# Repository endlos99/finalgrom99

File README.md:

FinalGROM 99
============

The *TI 99/4A FinalGROM Cartridge*, or FinalGROM 99 for short, is a
cartridge for the TI 99/4A home computer that allows you to run ROM and GROM
cartridge images from an SD card.  It succeeds the [FlashROM 99][3] released
in 2016.

The FinalGROM 99 supports ROM images, GROM images, and mixed images of up to
1 MB in size that use the write-to-ROM bank switching scheme.  The cartridge
does not require the Peripheral Expansion Box and runs on both PAL and NTSC
consoles, including modified consoles with an F18A.  It will also run on
v2.2 consoles and enables those to run ROM-only programs.

The cartridge offers some advanced modes that provide RAM and GRAM to
programs.  It also allows a running program to reload another program from
SD card or to dump its state to SD card.  All firmware of the FinalGROM 99
can be updated by SD card.

The FinalGROM 99 is released as Open Source Hardware under the
[CERN OHL license][5] and the [GNU GPL license][6].  Both hardware design
files and firmware sources are available on [GitHub][2].

The project homepage with detailed instructions is located at [GitHub][1].

Using the FinalGROM 99
----------------------

Using the FinalGROM 99 is simple and doesn't require any special hardware or
software.

To begin, copy some cartridge dumps or other images files onto an SD or SDHC
card.  You can create directories to organize your programs.  Switch off the
TI 99 and plug in the FinalGROM 99, then insert the SD card into the
FinalGROM 99.  Switch on the TI 99 and wait until the activity indicator on
the FinalGROM 99 is no longer lit.

Press any key to bring up the TI menu screen.  You should see the `FINALGROM
99` entry.  Select it to start the image browser, where you can page through
the list of available image entries with `,`, `.`, `SPACE`, and number keys.
When you descend into a folder, the FinalGROM will reload its contents from
the SD card.  To go back up to the parent folder, select the special folder
`/ ..`.

Select the image you want to run.  The screen will show a loader animation
while the image loads.  Once the image has been loaded, it will start
automatically.  The SD card is now no longer required and may be removed.

If only one image is found on the SD card, it is loaded immediately without
the need to select it first.  This method ensures maximum compatibility.
Note that ROM images loaded as single-image SD card will not run on v2.2
consoles!

If you want to run a different program from the SD card, reset the TI 99 by
pressing `FCTN-=` and then reset the FinalGROM 99 by pushing the reset
button.  If you do not reset the FinalGROM 99, the TI menu will show only
the previously selected image.  Alternatively, you can power cycle the
console, which will reset both TI 99 and FinalGROM 99.

For detailed usage information please refer to the [FinalGROM 99 homepage][1].

Building the FinalGROM 99
-------------------------

The [GitHub repository][2] contains all hardware design files and software
sources required to build the FinalGROM 99.

Building the FinalGROM 99 is slightly more involved than building its
predecessor [FlashROM 99][3], as the FinalGROM 99 uses surface-mounted
devices (SMD), of which two are programmable.  For starters, this
[video tutorial][12] shows how to solder SMD ICs by hand.

### Hardware

To build the FinalGROM 99, you need the following components:

- 1x FinalGROM 99 PCB
- 1x Xilinx XC95144XL-10TQ100 (TQFP-100)
- 1x Atmel ATmega 328P (TQPF-32)
- 1x Cypress SRAM CY62158EV30LL-45ZSXI (TSOP-44)
- 1x On Semiconductor Voltage Converter NCP1117ST33T3G (SOT-223)
- 12x 100 nF ceramic capacitors (SMD 0603)
- 2x 10 uF tantalum capacitors (SMD 0603)
- 2x 330 Ohm resistor (SMD 0603)
- 2x 10 kOhm resistor (SMD 0603)
- 1x LED 3-5 mm (through-hole)
- 2x micro push button (through-hole)
- 1x 2x3 socket (through-hole)
- 1x SD socket or Arduino SD shield

The FinalGROM 99 board was designed with [KiCad][7], a cross platform and
open source electronics design automation suite.  The design files are
stored in `pcb/` in the [repository][2].

The size of the 330 Ohm resistor depends on the color and brightness of your
LED.  For bright, red LEDs, 330 Ohm is a suitable value.

Both LED and push buttons are through-hole components, so that they can be
mounted on a cartridge shell and connected by wires to the board.

For the SD socket, you need a socket that has two little nubs at the bottom
of the socket.  Your best source for these is eBay, but check the pictures
before you buy.  Alternatively, you may use an Arduino SD shield that is
readily available online.  Make sure to pick a module that matches the
pin-out of the reference module shown below.  Note that the 5V input is not
used, so potential substitutes must be powered by 3.3V.

With some work, the FinalGROM 99 can be mounted in a standard TI 99
cartridge shell.

Please note that I don't offer carts, boards, or parts myself.

### Software

The firmware for the ATmega 328P consists of two components.  The `avr/`
folder contains the microcontroller logic for accessing the SD card,
generating the image browser, loading the selected image, and controlling
the CPLD.  The included bootloader enables firmware updates from an SD card.

The `ti/` folder contains TI 99 assembly sources for the image browser, the
GPL wrapper, and the help viewer.  The assembled machine code is embedded in
the microcontroller and loaded into RAM during operation.

To build the software, first run the `make.py` script in the `ti` folder.
You will need both `xas99` and `xga99` assemblers from the [xdt Suite][4] to
assemble the sources.  The script will also convert the generated machine
code into C code for the microcintroller.

    $ cd ti/
    $ ./make.py

The next step is to compile the microcontroller and bootloader code in
`avr/`.  The included `Makefile`s make the compilation trivial:

    $ cd avr/
    $ make
    $ cd boot/
    $ make

The last build yields a `package.hex` file containing both machine code
and bootloader.  You can flash the file to the ATmega 328P using
[`avrdude`][8] or any other programmer:

    $ avrdude -p m328p -P /dev/ttyACM0 -c stk500 -U flash:w:package.hex

Additionally, you need to program the lower fuse bits of the 328P so that it
runs at 8 Mhz:

    $ avrdude -p m328p -P /dev/ttyACM0 -c stk500 -U lfuse:w:0xe2:m

If you're using a different tool chain make sure to set `CKSEL3..0` in the
lower fuse byte to `0100`.  (Note that `0` means "programmed"/checked, and
`1` means "unprogrammed"/unchecked).

You can verify that you're running at the right clock speed by resetting
the FinalGROM 99 with no SD card inserted: The LED should blink about once
per second.

For future updates, you may copy the file `UPDATE.AVR` generated by the
first make in `avr/` to an SD card and start the FinalGROM 99 with it.  This
procedure will update the microcontroller similar to `avrdude`, but it does
not touch the bootloader.

Programming the CPLD requires the Xilinx [ISE 14.7 Web Pack][9] to generate
a JEDEC file or an XSVF file.  ISE Web Pack is freely available for Windows
and Linux.  After the installation, open ISE and open the project in
`vhdl/`.  Click on the little green arrow next to the process window to
generate a JEDED file.

The microcontroller contains an XSVF player to program the CPLD without JTAG
cable.  Generate the necessary XSVF file from the JEDED file by running (you
may have to adjust the path in `impact-batch`)

    $ cd vhdl/src
	$ ./impact-batch fg99-xsvf

Copy the resulting `.XSVF` file as `UPDATE.PLD` to an SD card and start the
FinalGROM 99 with it.  The cart will program the CPLD just like a JTAG cable
would do.

Once microcontroller and CPLD have been programmed, the assembled FinalGROM
99 is ready to use.

About the Project
-----------------

The TI 99/4A FinalGROM Cartridge is Open Source Hardware released under the
[CERN OHL license][5], in the hope that TI 99 enthusiasts may find it
useful.  Software components are released under the [GNU GPL license][6].

The microcontroller code uses a modified version of the [Petit FatFs][10]
library and an adapted version of the Xilinx [Application Note 58][11] code.

Heartfelt thanks go to Erik Spiehl (speccery) for helping me analyze an
electrical problem on the development boards, and to Jim Brain (Brain) for
showing me how to replace the Arduino shields by plain SD sockets.

Contributions to both hardware and software are very welcome!  Please email
feedback, support questions, inquiries for parts, and bug reports to the
developer at <r@0x01.de>.

[1]: https://endlos99.github.io/finalgrom99
[2]: https://github.com/endlos99/finalgrom99
[3]: https://endlos99.github.io/flashrom99
[4]: https://endlos99.github.io/xdt99
[5]: http://www.ohwr.org/projects/cernohl/wiki
[6]: http://www.gnu.org/licenses/gpl.html
[7]: http://kicad.org
[8]: http://www.nongnu.org/avrdude/
[9]: https://www.xilinx.com/products/design-tools/ise-design-suite/ise-webpack.html
[10]: http://elm-chan.org/fsw/ff/00index_p.html
[11]: http://www.xilinx.com/support/documentation/application_notes/xapp058.pdf
[12]: https://www.youtube.com/watch?v=6PB0u8irn-4

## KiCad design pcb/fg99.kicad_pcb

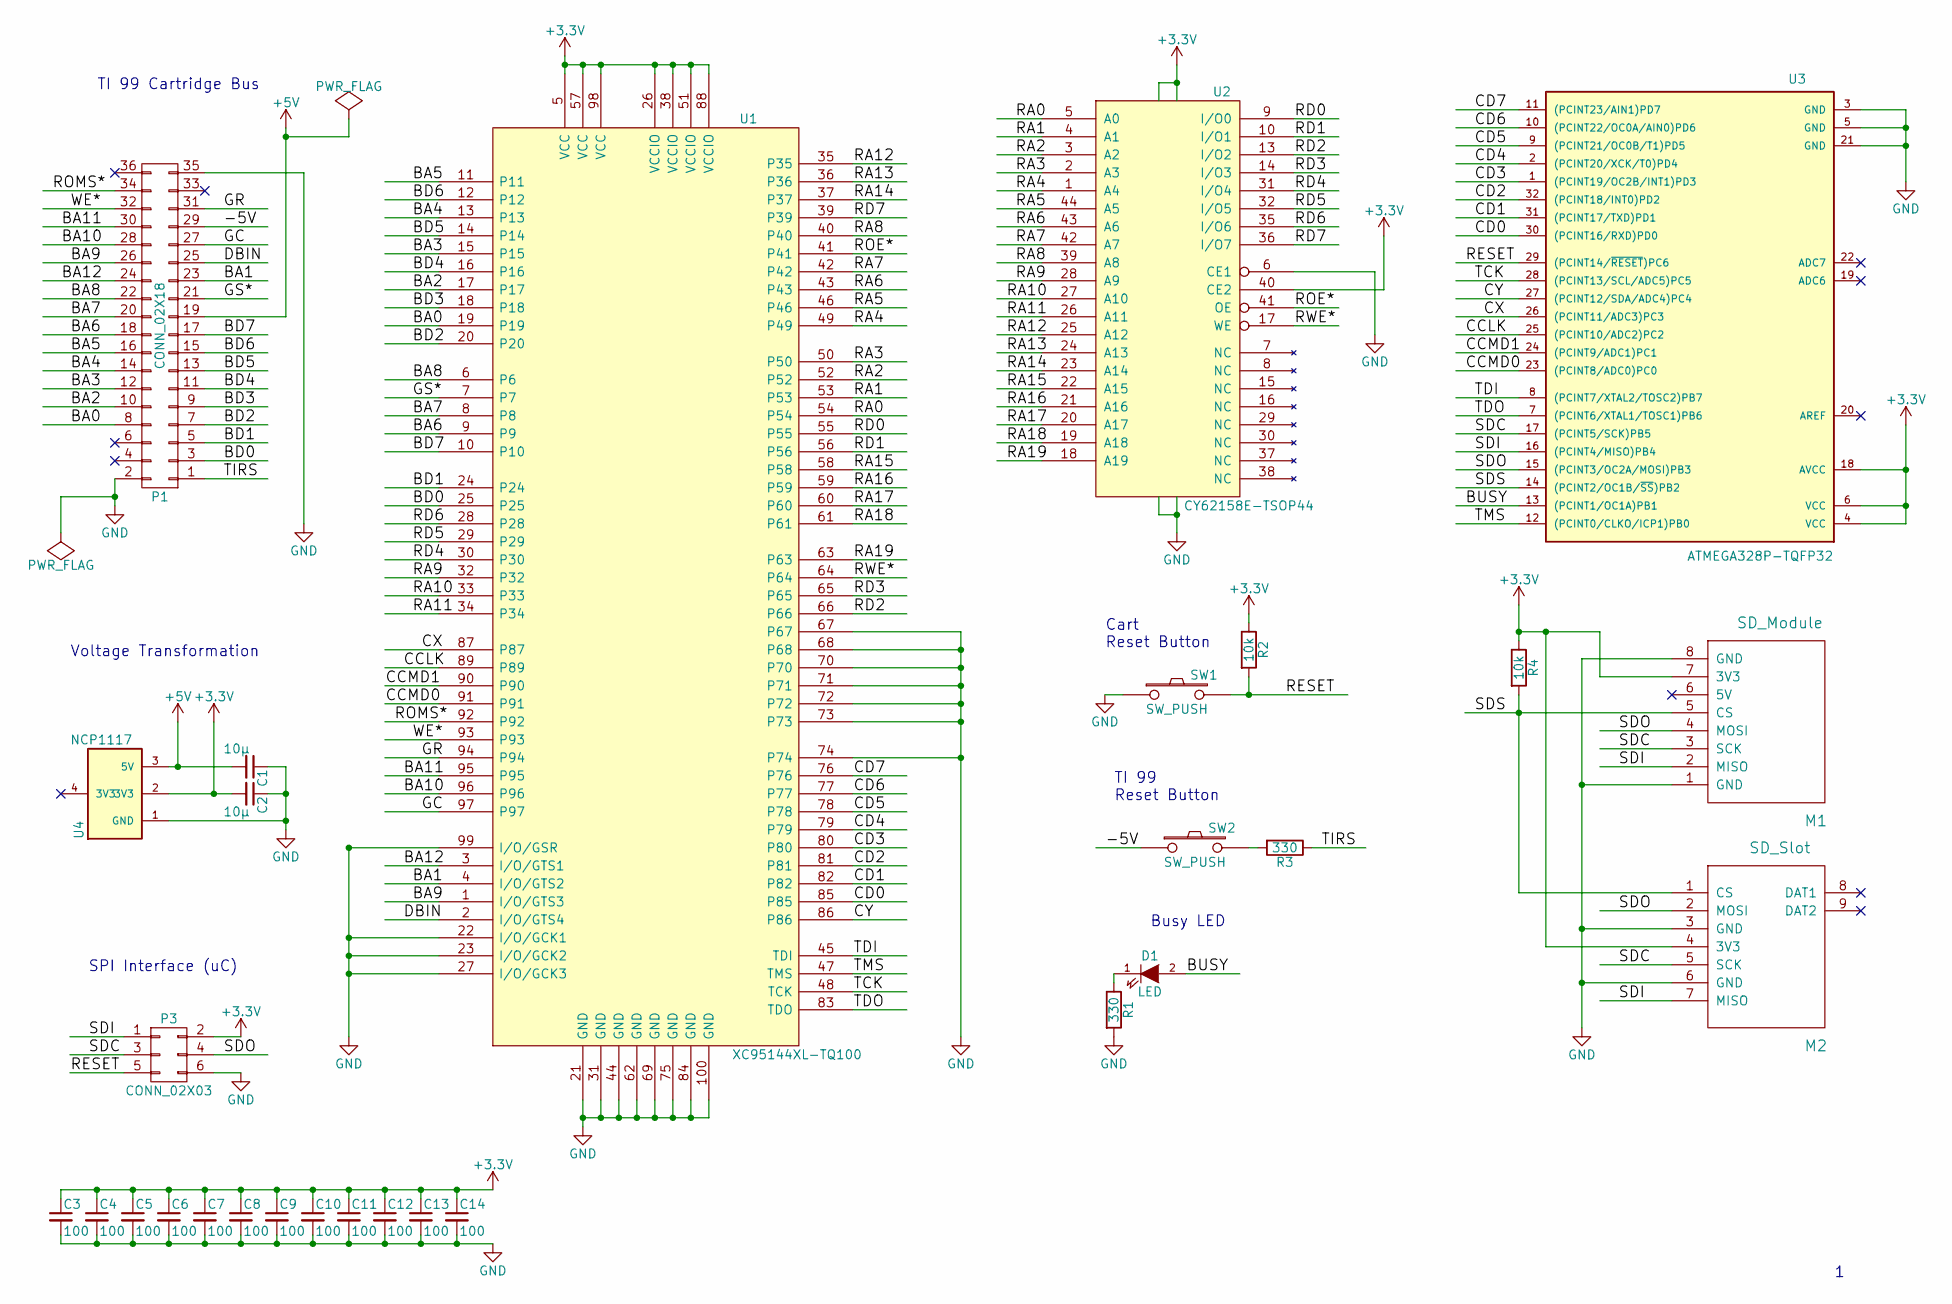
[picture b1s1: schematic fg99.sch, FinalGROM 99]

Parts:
C1, C2: 10µ; TantalC_SizeA_EIA-3216_Reflow; MFG Part No TAJA106K016RNJ
C3, C4, C5, C6, C7, C8, C9, C10, C11, C12, C13, C14: 100; C_0603; MFG Part No RND1500603B104J250
D1: LED; LED-5MM
M1: SD_Module; SD_MODULE_REV
M2: SD_Slot; SD-SOCKET
P1: CONN_02X18; CART_BUS
P3: CONN_02X03; IDC_Header_Straight_6pins
R1: 330; R_0603_T; MFG Part No RC0603FR-07330RL
R2, R4: 10k; R_0603_T; MFG Part No RC0603FR-0710KL
R3: 330; R_0603_T; MFG Part No RC0603FR-0710KL
SW1, SW2: SW_PUSH; SW_PUSH_6mm
U1: XC95144XL-TQ100; TQFP-100_14x14mm_Pitch0.5mm; MFG Part No XC95144XL-10TQG100C
U2: CY62158E-TSOP44; TSOP-44; MFG Part No CY62158ELL-45ZSXIT
U3: ATMEGA328P-TQFP32; TQFP-32_7x7mm_Pitch0.8mm; MFG Part No ATMEGA328P-AU
U4: NCP1117; SOT-223; MFG Part No NCP1117ST33T3G

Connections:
+3V3: C2.2, C3.1, C4.1, C5.1, C6.1, C7.1, C8.1, C9.1, C10.1, C11.1, C12.1, C13.1, C14.1, M1.7 (3V3), M2.4 (3V3), P3.2, R2.1, R4.1, U1.5 (VCC), U1.26 (VCCIO), U1.38 (VCCIO), U1.51 (VCCIO), U1.57 (VCC), U1.88 (VCCIO), U1.98 (VCC), U2.11 (VCC), U2.33 (VCC), U2.40 (CE2), U3.4 (VCC), U3.6 (VCC), U3.18 (AVCC), U4.2 (3V3)
+5V: C1.2, P1.19, U4.3 (5V)
/-5V: P1.29, SW2.1
/BA0: P1.8, U1.19
/BA1: P1.23, U1.4 (I/O/GTS2)
/BA2: P1.10, U1.17
/BA3: P1.12, U1.15
/BA4: P1.14, U1.13
/BA5: P1.16, U1.11
/BA6: P1.18, U1.9
/BA7: P1.20, U1.8
/BA8: P1.22, U1.6
/BA9: P1.26, U1.1 (I/O/GTS3)
/BA10: P1.28, U1.96
/BA11: P1.30, U1.95
/BA12: P1.24, U1.3 (I/O/GTS1)
/BD0: P1.3, U1.25
/BD1: P1.5, U1.24
/BD2: P1.7, U1.20
/BD3: P1.9, U1.18
/BD4: P1.11, U1.16
/BD5: P1.13, U1.14
/BD6: P1.15, U1.12
/BD7: P1.17, U1.10
/BUSY: D1.2 (A), U3.13 ((PCINT1/OC1A)PB1)
/CCLK: U1.89, U3.25 ((PCINT10/ADC2)PC2)
/CCMD0: U1.91, U3.23 ((PCINT8/ADC0)PC0)
/CCMD1: U1.90, U3.24 ((PCINT9/ADC1)PC1)
/CD0: U1.85, U3.30 ((PCINT16/RXD)PD0)
/CD1: U1.82, U3.31 ((PCINT17/TXD)PD1)
/CD2: U1.81, U3.32 ((PCINT18/INT0)PD2)
/CD3: U1.80, U3.1 ((PCINT19/OC2B/INT1)PD3)
/CD4: U1.79, U3.2 ((PCINT20/XCK/T0)PD4)
/CD5: U1.78, U3.9 ((PCINT21/OC0B/T1)PD5)
/CD6: U1.77, U3.10 ((PCINT22/OC0A/AIN0)PD6)
/CD7: U1.76, U3.11 ((PCINT23/AIN1)PD7)
/CX: U1.87, U3.26 ((PCINT11/ADC3)PC3)
/CY: U1.86, U3.27 ((PCINT12/SDA/ADC4)PC4)
/DBIN: P1.25, U1.2 (I/O/GTS4)
/GC: P1.27, U1.97
/GR: P1.31, U1.94
/GS*: P1.21, U1.7
/RA0: U1.54, U2.5 (A0)
/RA1: U1.53, U2.4 (A1)
/RA2: U1.52, U2.3 (A2)
/RA3: U1.50, U2.2 (A3)
/RA4: U1.49, U2.1 (A4)
/RA5: U1.46, U2.44 (A5)
/RA6: U1.43, U2.43 (A6)
/RA7: U1.42, U2.42 (A7)
/RA8: U1.40, U2.39 (A8)
/RA9: U1.32, U2.28 (A9)
/RA10: U1.33, U2.27 (A10)
/RA11: U1.34, U2.26 (A11)
/RA12: U1.35, U2.25 (A12)
/RA13: U1.36, U2.24 (A13)
/RA14: U1.37, U2.23 (A14)
/RA15: U1.58, U2.22 (A15)
/RA16: U1.59, U2.21 (A16)
/RA17: U1.60, U2.20 (A17)
/RA18: U1.61, U2.19 (A18)
/RA19: U1.63, U2.18 (A19)
/RD0: U1.55, U2.9 (I/O0)
/RD1: U1.56, U2.10 (I/O1)
/RD2: U1.66, U2.13 (I/O2)
/RD3: U1.65, U2.14 (I/O3)
/RD4: U1.30, U2.31 (I/O4)
/RD5: U1.29, U2.32 (I/O5)
/RD6: U1.28, U2.35 (I/O6)
/RD7: U1.39, U2.36 (I/O7)
/RESET: P3.5, R2.2, SW1.2, U3.29 ((PCINT14/~RESET~)PC6)
/ROE*: U1.41, U2.41 (OE)
/ROMS*: P1.34, U1.92
/RWE*: U1.64, U2.17 (WE)
/SDC: M1.3 (SCK), M2.5 (SCK), P3.3, U3.17 ((PCINT5/SCK)PB5)
/SDI: M1.2 (MISO), M2.7 (MISO), P3.1, U3.16 ((PCINT4/MISO)PB4)
/SDO: M1.4 (MOSI), M2.2 (MOSI), P3.4, U3.15 ((PCINT3/OC2A/MOSI)PB3)
/SDS: M1.5 (CS), M2.1 (CS), R4.2, U3.14 ((PCINT2/OC1B/~SS~)PB2)
/TCK: U1.48 (TCK), U3.28 ((PCINT13/SCL/ADC5)PC5)
/TDI: U1.45 (TDI), U3.8 ((PCINT7/XTAL2/TOSC2)PB7)
/TDO: U1.83 (TDO), U3.7 ((PCINT6/XTAL1/TOSC1)PB6)
/TIRS: P1.1, R3.1
/TMS: U1.47 (TMS), U3.12 ((PCINT0/CLKO/ICP1)PB0)
/WE*: P1.32, U1.93
GND: C1.1, C2.1, C3.2, C4.2, C5.2, C6.2, C7.2, C8.2, C9.2, C10.2, C11.2, C12.2, C13.2, C14.2, M1.1 (GND), M1.8 (GND), M2.3 (GND), M2.6 (GND), P1.2, P1.35, P3.6, R1.2, SW1.1, U1.21 (GND), U1.22 (I/O/GCK1), U1.23 (I/O/GCK2), U1.27 (I/O/GCK3), U1.31 (GND), U1.44 (GND), U1.62 (GND), U1.67, U1.68, U1.69 (GND), U1.70, U1.71, U1.72, U1.73, U1.74, U1.75 (GND), U1.84 (GND), U1.99 (I/O/GSR), U1.100 (GND), U2.6 (CE1), U2.12 (GND), U2.34 (GND), U3.3 (GND), U3.5 (GND), U3.21 (GND), U4.1 (GND)
unnamed: D1.1 (K), R1.1
unnamed: R3.2, SW2.2

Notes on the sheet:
Voltage Transformation
TI 99 Reset Button
Busy LED
TI 99 Cartridge Bus
SPI Interface (uC)
Cart Reset Button

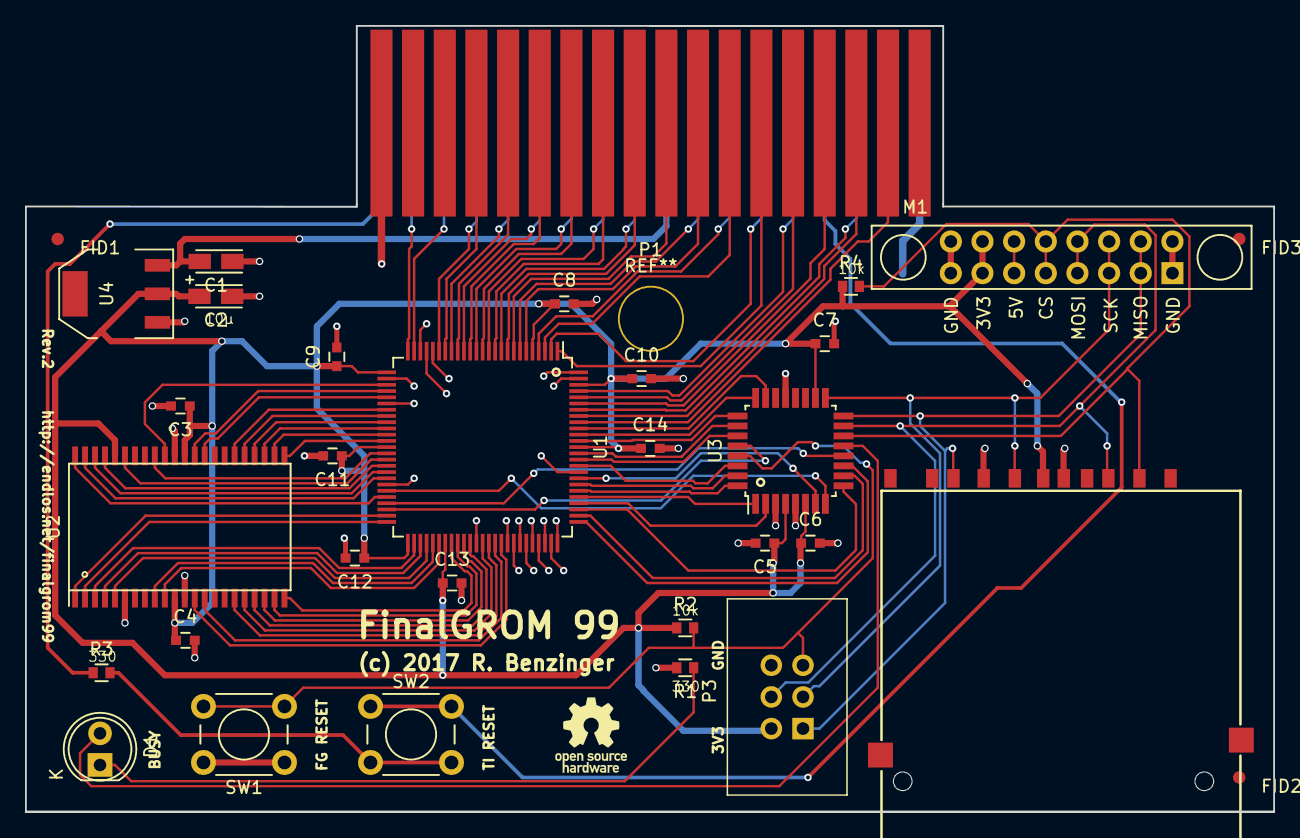
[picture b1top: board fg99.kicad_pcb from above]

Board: 2 copper layers, 100.1 x 63.1 mm, 32 parts (0 on the bottom side), 87 nets.

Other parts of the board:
FID1, FID2, FID3: Fiducial_1mm_Dia_2.54mm_Outer_CopperTop

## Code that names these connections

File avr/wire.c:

/*
 * wire.c: low-level signal handling
 */


#include <avr/io.h>
#include <util/delay.h>

#include "wire.h"


/*
 * pins
 *
 * B7  TDI                     D7  CD7
 * B6  TDO       C6  RESET     D6  CD6
 * B5  SDC       C5  TCK       D5  CD5
 * B4  SDI (MI)  C4  CCMD0(CY) D4  CD4
 * B3  SDO (MO)  C3  CX        D3  CD3
 * B2  SDS       C2  CCLK      D2  CD2
 * B1  BUSY      C1  CCMD2     D1  CD1
 * B0  TMS       C0  CCMD1     D0  CD0
 */

#define pTDI    (1 << PB7)
#define pTDO    (1 << PB6)
#define pSDC    (1 << PB5)
#define pSDI    (1 << PB4)
#define pSDO    (1 << PB3)
#define pSDS    (1 << PB2)
#define pBUSY   (1 << PB1)
#define pTMS    (1 << PB0)

#define pRESET  (1 << PC6)
#define pTCK    (1 << PC5)
#define pCCMD0  (1 << PC4)
#define pCX     (1 << PC3)
#define pCCLK   (1 << PC2)
#define pCCMD2  (1 << PC1)
#define pCCMD1  (1 << PC0)
#define pC      0x1f

#define sRUN    (                           pCCLK)        // 000
#define sSIZE   (pCCMD2                   | pCCLK | pCX)  // 100
#define sCONF   (pCCMD2 |          pCCMD0 | pCCLK | pCX)  // 101
#define sDUMP   (pCCMD2 | pCCMD1          | pCCLK | pCX)  // 110
#define sLOAD   (pCCMD2 | pCCMD1 | pCCMD0 | pCCLK | pCX)  // 111

static uint8_t listen_sequence[] = {
  0x99, 'O', 'K', 'F', 'G', '9', '9', 0x99, 0x00
};


/*
 * init pins
 */

void init()
{
  // SPI and JTAG, busy indicator
  DDRB = pBUSY;  // keep pins inactive
  PORTB = 0x00;
   // control lines
  DDRC = pC;
  PORTC = sLOAD;  // LOAD/RLOAD
  // data µC <-> CPLD
  DDRD = 0xff;
  PORTD = 0x00;
}


/*
 * transfer RAM data to CPLD
 */

// write byte stream
void writeBegin()
{
  DDRC |= pCX;  // CX used for RWE
  PORTC = sLOAD;  // LOAD/RLOAD
  _delay_us(7);  // time for CPLD to pick up value (3+ clocks)
  DDRD = 0xff;  // CDX sends
  // cart offline now
}


// write single byte
void writeByte(uint8_t b)
{
  // CCLK high
  PORTD = b;
  PORTC &= ~pCCLK;  // CCLK low
  PORTC &= ~pCX;  // RWE low
  // read CDX data
  PORTC |= pCX;  // RWE high
  PORTC |= pCCLK;  // CCLK high
}


// sets start addr and sizing information
//   size = 1 r - X X X X X = GROM mask (r=0 reset)
//          0 X X X X X X X = bank mask
void writeSize(uint8_t size) //OK
{
  PORTD = size;
  PORTC = sSIZE;  // set size
  _delay_us(7);
  PORTC &= ~pCCLK;  // CCLK low
  PORTC |= pCCLK;  // CCLK high -> read size
  _delay_us(0.2);
  PORTC = sLOAD;  // clear set size
  _delay_us(7);
}


// cartridge configurations
void setConfig(uint8_t config)
{
  PORTC = sCONF;
  PORTD = config;
  _delay_us(7);
  PORTC = sLOAD;
  _delay_us(7);
}


void writeEnd()
{
}


/*
 * read TI data via serial connection
 * - clock: CLR @>6000
 * - send:  CLR @>7xyz, where xyz = 2*byte to send
 */

void receiveBegin()
{
  DDRC &= ~pCX;  // CX used for SCLK
  PORTD = 0x00;  // CDX receives
  DDRD = 0x00;
  PORTC = sRUN;  // RUN/-
  _delay_us(7);
  // cart online again
}


void receiveBytes(uint8_t *buffer, uint8_t length, uint8_t needs_seq)
{
  // get to known state (IMGEN low), initial CLR @>6000 comes too late
  while (PINC & pCX);  // read CX/SCLK

  // look for listen sequence if needed
  while (needs_seq) {
    uint8_t *p = listen_sequence;
    while (*p) {
      while (!(PINC & pCX));  // wait for high clock
      uint8_t b = PIND;  // read byte
      while (PINC & pCX);  // wait for low clock
      if (b != *p)
        break;  // redo sequence
      ++p;
    }
    if (!*p)
      needs_seq = 0;  // received complete sequence
  }

  // read bytes from TI
  for (uint8_t i = length; i > 0; --i) {
    // wait for clock bit (SCLK)
    while (!(PINC & pCX));
    // read byte
    *buffer++ = PIND;
    // wait until SCLK low again
    while (PINC & pCX);
  }
}


void receiveEnd()
{
  PORTC = sLOAD;  // cart offline
  _delay_us(7);
}


/*
 * transfer RAM data to uC/SD
 */

void readBegin()
{
  PORTD = 0x00;  // CDX receives
  DDRD = 0x00;
  PORTC = sDUMP;  // LOAD/RDUMP
  _delay_us(7);
  // cart offline for dump
}


uint8_t readByte()
{
  uint8_t b = PIND;
  PORTC &= ~pCCLK;  // next byte
  PORTC |= pCCLK;
  return b;
}


void readEnd()
{
  // followed by receiveBegin()
}


/*
 * activity indicator
 */

void led(uint8_t on)
{
  if (on) {
    PORTB |= pBUSY;
  } else {
    PORTB &= ~pBUSY;
  }
}


/*
 * fatal error: blink LED
 */

void flash_error(const uint8_t count)
{
  while(1) {
    for (uint8_t i = 0; i < count; ++i) {
      led(1);
      _delay_ms(250);
      led(0);
      _delay_ms(250);
    }
    _delay_ms(600);
  }
}

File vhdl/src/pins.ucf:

# FinalGROM 99 on XC95144XL

NET ROMS       LOC="P92";
NET WE         LOC="P93";
NET GR         LOC="P94";
NET GC         LOC="P97";
NET DBIN       LOC="P2";
NET GS         LOC="P7";

NET BUS_DX(7)  LOC="P10";
NET BUS_DX(6)  LOC="P12";
NET BUS_DX(5)  LOC="P14";
NET BUS_DX(4)  LOC="P16";
NET BUS_DX(3)  LOC="P18";
NET BUS_DX(2)  LOC="P20";
NET BUS_DX(1)  LOC="P24";
NET BUS_DX(0)  LOC="P25";

NET BUS_AX(12) LOC="P3";
NET BUS_AX(11) LOC="P95";
NET BUS_AX(10) LOC="P96";
NET BUS_AX(9)  LOC="P1";
NET BUS_AX(8)  LOC="P6";
NET BUS_AX(7)  LOC="P8";
NET BUS_AX(6)  LOC="P9";
NET BUS_AX(5)  LOC="P11";
NET BUS_AX(4)  LOC="P13";
NET BUS_AX(3)  LOC="P15";
NET BUS_AX(2)  LOC="P17";
NET BUS_AX(1)  LOC="P4";
NET BUS_AX(0)  LOC="P19";

NET RAM_DX(7)  LOC="P39";
#NET RAM_DX(7)  LOC="P67";
NET RAM_DX(6)  LOC="P28";
NET RAM_DX(5)  LOC="P29";
NET RAM_DX(4)  LOC="P30";
NET RAM_DX(3)  LOC="P65";
NET RAM_DX(2)  LOC="P66";
NET RAM_DX(1)  LOC="P56";
NET RAM_DX(0)  LOC="P55";

NET RAM_AX(19) LOC="P63";
NET RAM_AX(18) LOC="P61";
NET RAM_AX(17) LOC="P60";
NET RAM_AX(16) LOC="P59";
NET RAM_AX(15) LOC="P58";
NET RAM_AX(14) LOC="P37";
NET RAM_AX(13) LOC="P36";
NET RAM_AX(12) LOC="P35";
NET RAM_AX(11) LOC="P34";
NET RAM_AX(10) LOC="P33";
NET RAM_AX(9)  LOC="P32";
NET RAM_AX(8)  LOC="P40";
NET RAM_AX(7)  LOC="P42";
NET RAM_AX(6)  LOC="P43";
NET RAM_AX(5)  LOC="P46";
NET RAM_AX(4)  LOC="P49";
NET RAM_AX(3)  LOC="P50";
NET RAM_AX(2)  LOC="P52";
NET RAM_AX(1)  LOC="P53";
NET RAM_AX(0)  LOC="P54";

NET RAM_WE     LOC="P64";
NET RAM_OE     LOC="P41";

NET CCLK       LOC="P89";
NET CX         LOC="P87";  # RWE/SCLK

NET CCMD(2)    LOC="P90";
NET CCMD(1)    LOC="P91";
NET CCMD(0)    LOC="P86";  # CY

NET CDX(7)     LOC="P76";
NET CDX(6)     LOC="P77";
NET CDX(5)     LOC="P78";
NET CDX(4)     LOC="P79";
NET CDX(3)     LOC="P80";
NET CDX(2)     LOC="P81";
NET CDX(1)     LOC="P82";
NET CDX(0)     LOC="P85";

#NET TDI        LOC="P45";
#NET TMS        LOC="P47";
#NET TCK        LOC="P48";
#NET TDO        LOC="P83";

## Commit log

2017-05-02 FG99: add documentation
2017-05-02 add pre-release documentation
2017-06-05 update release date
2017-07-09 FinalGROM 99 release
2017-07-28 fix typos in manual
2017-07-29 fix slow SD cards, release update 1.1
2017-07-29 publish update 1.1
2017-07-30 amend update 1.1, ignore hidden and system files and folders
2017-07-30 update version 1.1 patch
2017-08-03 update patch 1.1: make version legible
2017-08-03 clarify update procedure
2017-08-31 add cart shell providers
2017-08-31 revise shell offerings
2017-11-15 minor update
2017-11-24 restore previous page, with minor improvements
2017-11-24 update manual
2017-11-24 update 1.2: enable mixed images for dumping
2017-11-24 add missing code changes for version 1.2
2017-11-24 add update 1.2 to home page
2017-11-24 update dump section
2017-11-24 fix style typos
2017-11-24 update dump section in manual
2018-03-17 add ebay note to homepage
2018-03-17 update documentation
2018-03-22 update 1.3: show programs of images with subprograms again
2018-03-22 add update 1.3 to homepage
2018-07-11 Removed label from available options
2018-10-27 restore homepage
2019-02-23 update S&H
2019-02-23 update 'where to get' in manual
2019-04-09 restore page
2019-08-16 update CPLD firmware to fix Minimem bug
2019-08-16 add download of latest firmware
2019-10-28 remove remaining latch (to fix Minimem bug)
2019-10-28 update 'Where to get' section
2020-10-05 convert make.py to Python 3
2021-01-07 add HEX file for AVR
2021-02-16 fix SRAM IC specification
2021-11-09 Update README.md
    https://forum.kicad.info/t/warning-avoid-all-links-to-kicad-pcb-org-use-kicad-org/31521
2021-11-21 Fix typo in CPLD upgrade
2023-08-12 Include firmwares for QI consoles (written by Jochen Buur)
2023-08-19 Add Gerber files for PCB

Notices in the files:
pcb/fg99.kicad_pcb:
Copyright (c) 2017 Ralph Benzinger
Released as Open Source Hardware under CERN OHL 1.2 and GNU GPL 3 licenses
(c) 2017 R. Benzinger
